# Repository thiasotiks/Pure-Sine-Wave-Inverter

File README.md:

# Pure-Sine-Wave-Inverter    
This repository includes codes for pure sine wave inverter @ 50 Hz, 220 V
It also contains the PCB design files in a seperate zip file

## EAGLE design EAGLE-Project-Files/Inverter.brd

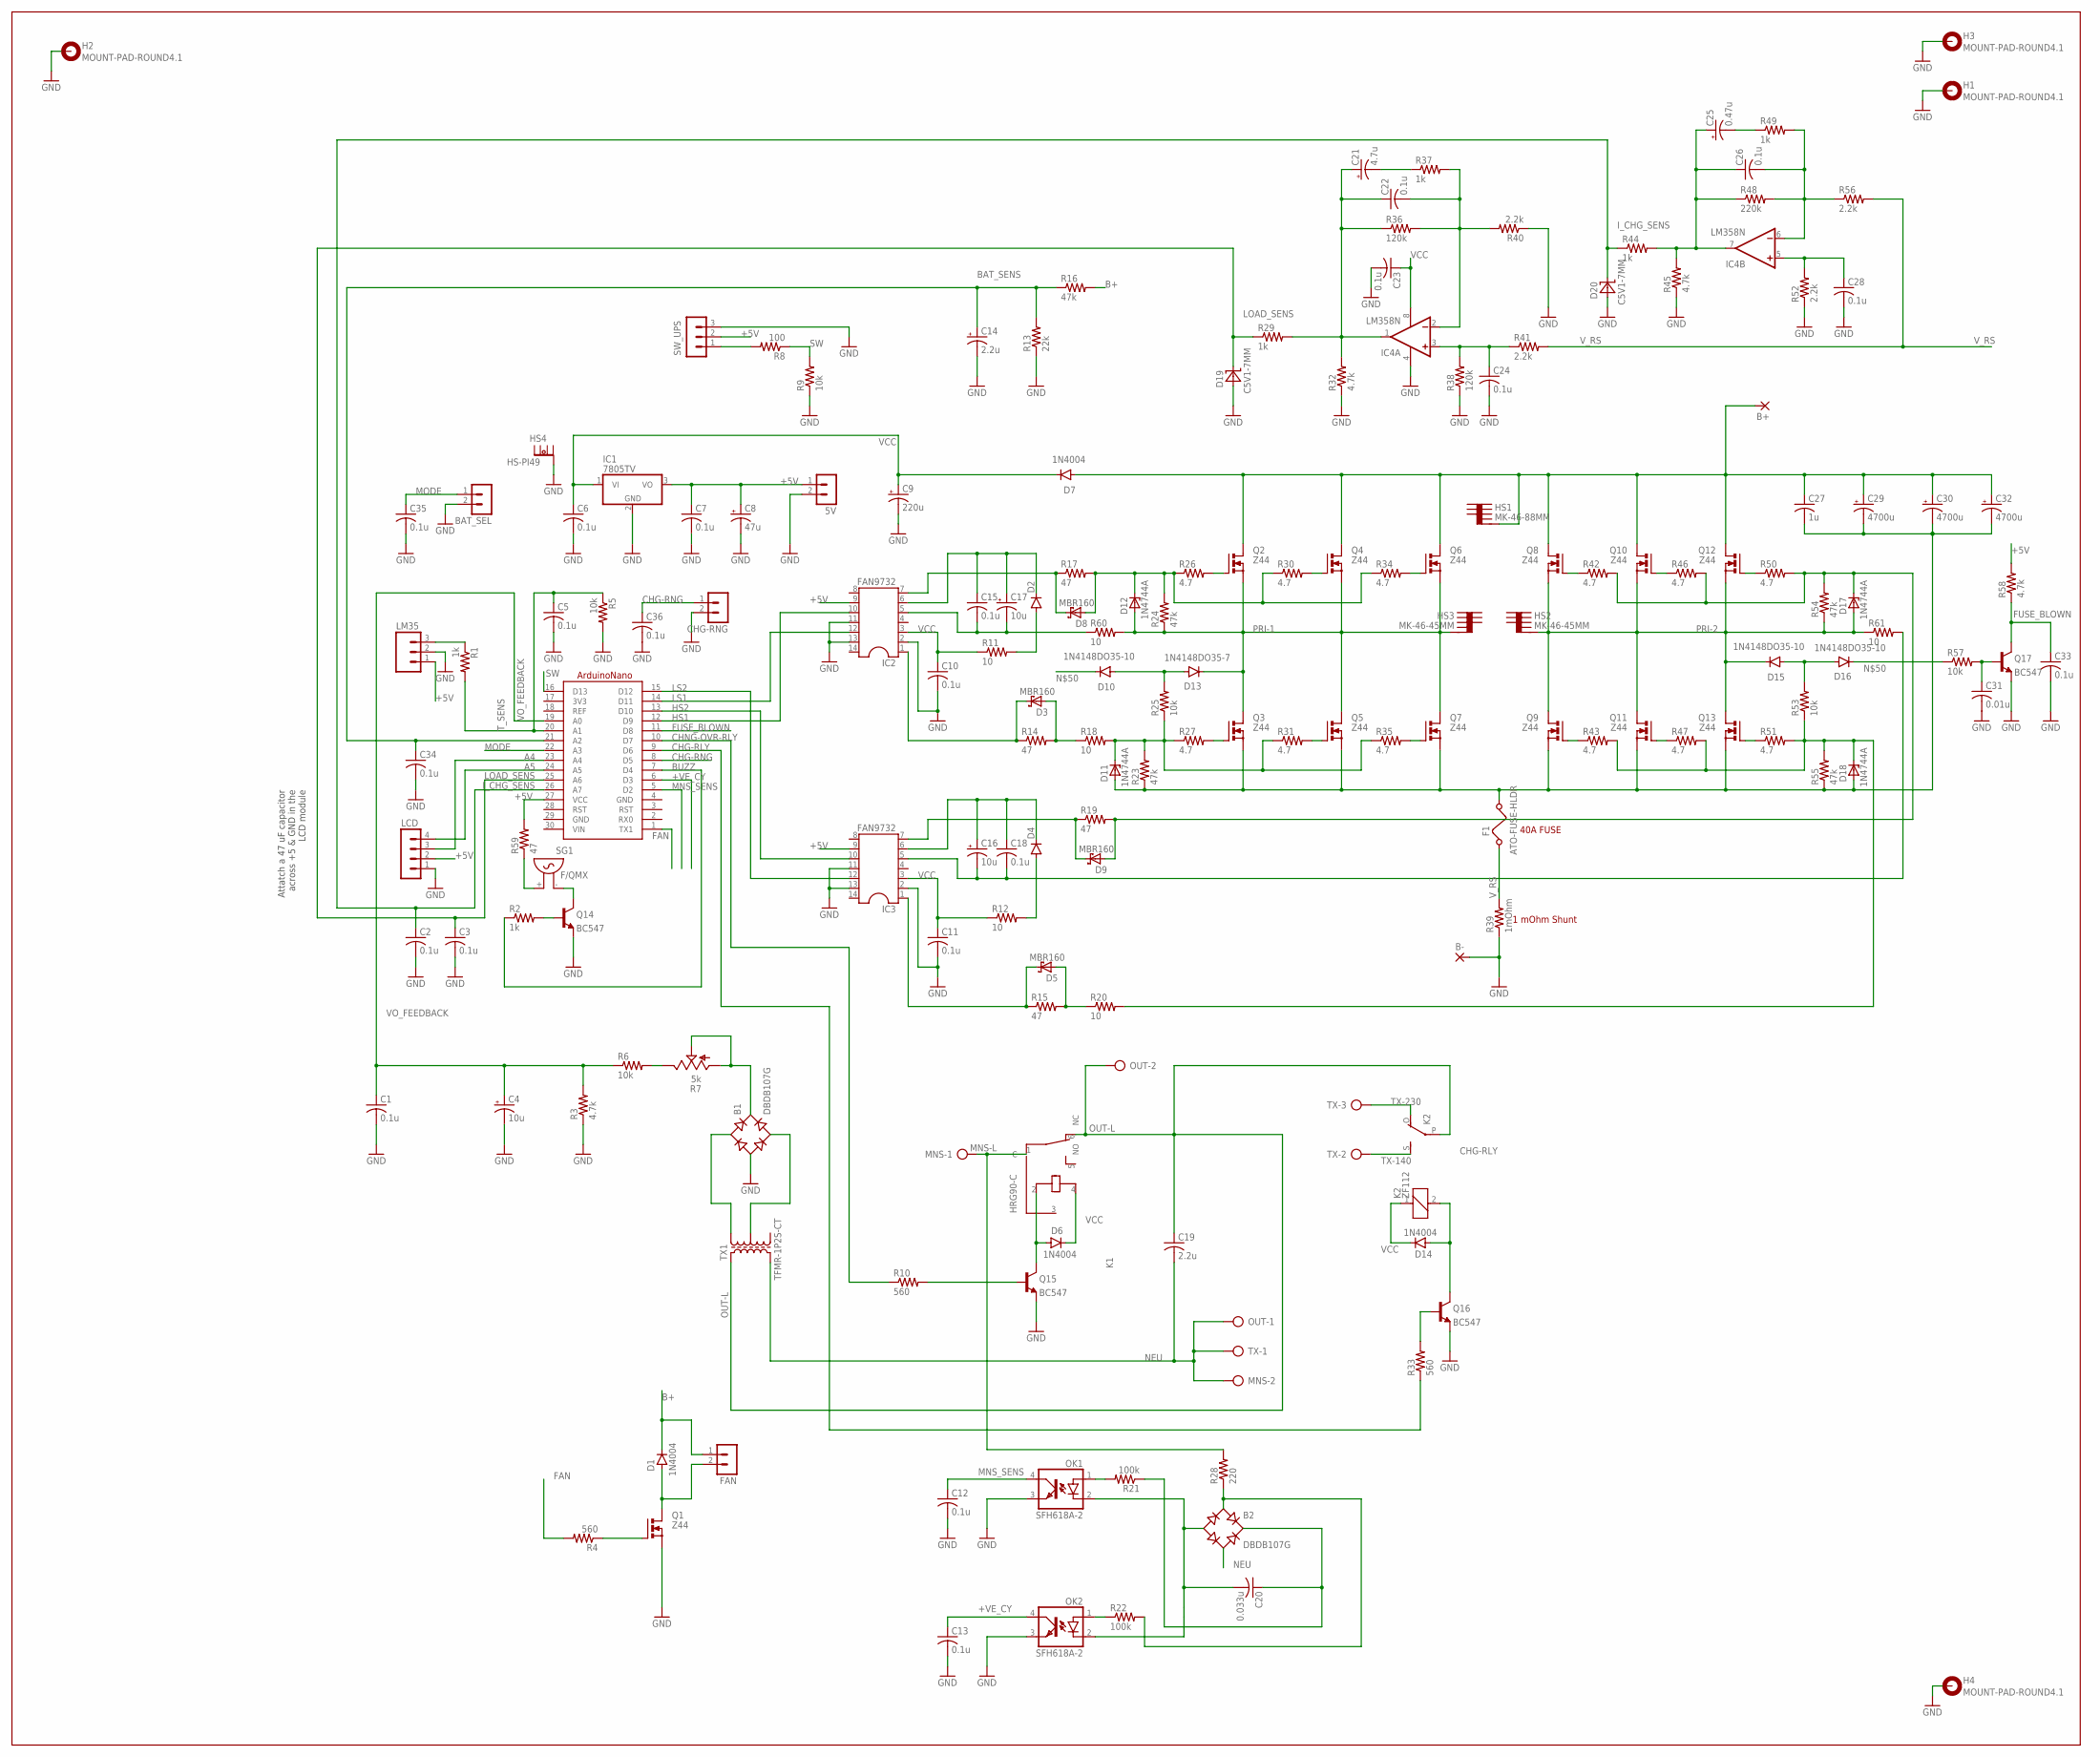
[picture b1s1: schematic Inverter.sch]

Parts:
5V: MA02-1
A1: ARDUINONANO-MIN-TXT; ARDUINONANO-MINIMUM-TXT
B1, B2: DBDB107G; DB
B+: 3,17/1,1
B-: 3,17/1,1
BAT_SEL: MA02-1
C1, C2, C3, C5, C6, C7, C10, C11, C12, C13, C15, C18, C22, C23, C24, C26, C28, C33, C34, C35, C36: 0.1u; C025-025X050
C4, C16, C17: 10u; E2,5-6E
C8: 47u; E2,5-6E
C9: 220u; E2,5-6E
C14: 2.2u; E2,5-6
C19: 2.2u; C230-85X245
C20: 0.033u; C050-025X075
C21: 4.7u; E2,5-6
C25: 0.47u; E2,5-6
C27: 1u; C225-113X268
C29, C30, C32: 4700u; EB20D
C31: 0.01u; C025-025X050
CHG-RNG: MA02-1
D1, D6, D7, D14: 1N4004; DO41-10
D2, D4, D10, D15, D16: 1N4148DO35-10; DO35-10
D3, D5, D8, D9: MBR160; DO41-10
D11, D12, D17, D18: 1N4744A; DO41Z10
D13: 1N4148DO35-7; DO35-7
D19, D20: C5V1-7MM; DO35-7
F1: ATO-FUSE-HLDR; ATO-FUSE-HOLDER
FAN: MA02-1
H1, H2, H3, H4: MOUNT-PAD-ROUND4.1; 4,1-PAD
HS1: MK-46-88MM
HS2, HS3: MK-46-45MM
HS4: HS-PI49; PI49-20MM
IC1: 7805TV; TO220V
IC2, IC3: FAN9732; SOCKET-14
IC4: LM358N; DIL08
K1: HRG90-C; T90-C
K2: ZF112
LCD: MA04-1
LM35: MA03; 03P
MNS: AK300/2
OK1, OK2: SFH618A-2; DIP4
OUT: AK300/2
Q1, Q2, Q3, Q4, Q5, Q6, Q7, Q8, Q9, Q10, Q11, Q12, Q13: Z44; TO220BV
Q14, Q15, Q16, Q17: BC547; TO92_LIN
R1, R2, R29, R37, R44, R49: 1k; 0207/10
R3, R32, R45, R58: 4.7k; 0207/10
R4, R10, R33: 560; 0207/10
R5, R6, R9, R25, R53, R57: 10k; 0207/10
R7: 5k; CA6V
R8: 100; 0207/10
R11, R12, R18, R20, R60, R61: 10; 0207/10
R13: 22k; 0207/10
R14, R15, R17, R19, R59: 47; 0207/10
R16, R23, R24, R54, R55: 47k; 0207/10
R21: 100k; 0411V
R22: 100k; 0411/15
R26, R27, R30, R31, R34, R35, R42, R43, R46, R47, R50, R51: 4.7; 0207/10
R28: 220; 0207/10
R36, R38: 120k; 0207/10
R39: 1mOhm; SHUNT-R
R40, R41, R52, R56: 2.2k; 0207/10
R48: 220k; 0207/10
SG1: F/QMX
SW_UPS: MA03-1
TX: AK300/3
TX1: TRANSFORMER-1P2S-CT; XFMR-1S2P-CT-41X34MM

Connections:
3V3: A1.17 (3V3)
+5V: 5V.1, A1.27 (VCC), C7.1, C8.+, IC1.3 (VO), IC2.9, IC3.9, LCD.2, LM35.1, R58.2, R59.2, SW_UPS.2
+VE_CY: A1.6 (D3), C13.1, OK2.4 (COL)
A4: A1.23 (A4), LCD.3
A5: A1.24 (A5), LCD.4
B+: B+.1, C27.1, C29.+, C30.+, C32.+, D1.C, D7.A, FAN.1, HS1.1, HS1.2, Q2.D, Q4.D, Q6.D, Q8.D, Q10.D, Q12.D, R16.2
BAT_SENS: A1.21 (A2), C14.+, C34.1, R13.2, R16.1
BUZZ: A1.7 (D4), R2.1
CHG-RLY: A1.9 (D6), R33.1
CHG-RNG: A1.8 (D5), C36.1, CHG-RNG.1
CHNG-OVR-RLY: A1.10 (D7), R10.1
FAN: A1.1 (TX1), R4.2
FUSE_BLOWN: A1.11 (D8), C33.1, Q17.3 (C), R58.1
GND: 5V.2, A1.4 (GND), A1.29 (GND), B1.-, B-.1, BAT_SEL.2, C1.2, C2.2, C3.2, C4.-, C5.2, C6.2, C7.2, C8.-, C9.-, C10.2, C11.2, C12.2, C13.2, C14.-, C23.2, C24.2, C28.2, C31.2, C33.2, C34.2, C35.2, C36.2, CHG-RNG.2, D19.A, D20.A, H1.B4,1, H2.B4,1, H3.B4,1, H4.B4,1, HS4.1, HS4.2, IC1.2 (GND), IC2.2, IC2.11, IC2.13, IC3.2, IC3.11, IC3.13, IC4.4 (V-), LCD.1, LM35.2, OK1.3 (EMIT), OK2.3 (EMIT), Q1.S, Q14.1 (E), Q15.1 (E), Q16.1 (E), Q17.1 (E), R3.1, R5.2, R9.1, R13.1, R32.1, R38.1, R39.P$1 (1), R40.1, R45.1, R52.1, SW_UPS.3
HS1: A1.12 (D9), IC2.10
HS2: A1.13 (D10), IC3.10
I_CHG_SENS: A1.26 (A7), C2.1, D20.C, R44.1
LOAD_SENS: A1.25 (A6), C3.1, D19.C, R29.1
LS1: A1.14 (D11), IC2.12
LS2: A1.15 (D12), IC3.12
MNS-L: K1.1 (C), MNS.1, R28.2
MNS_SENS: A1.5 (D2), C12.1, OK1.4 (COL)
MODE: A1.22 (A3), BAT_SEL.1, C35.1
unnamed: D4.A, R12.2
unnamed: Q15.2 (B), R10.2
unnamed: C15.1, C17.+, D2.C, IC2.6
unnamed: C16.+, C18.1, D4.C, IC3.6
unnamed: Q14.3 (C), SG1.- (1)
unnamed: D8.A, D12.C, R17.2, R24.2, R26.1, R30.1, R34.1
unnamed: D2.A, R11.2
unnamed: D8.C, IC2.7, R17.1
unnamed: D3.C, IC2.1, R14.1
unnamed: D9.C, IC3.7, R19.1
unnamed: D5.C, IC3.1, R15.1
unnamed: D11.C, R18.2, R23.2, R25.1, R27.1, R31.1, R35.1
unnamed: C27.2, C29.-, C30.-, C32.-, D11.A, D18.A, F1.P$2 (2), Q3.S, Q5.S, Q7.S, Q9.S, Q11.S, Q13.S, R23.1, R55.1
unnamed: D9.A, D17.C, R19.2, R42.2, R46.2, R50.2, R54.2
unnamed: D18.C, R20.2, R43.2, R47.2, R51.2, R53.1, R55.2
unnamed: Q2.G, R26.2
unnamed: C24.1, IC4.3 (+IN), R38.2, R41.1
unnamed: B1.AC1, TX1.10
unnamed: C16.-, C18.2, IC3.5, R61.2
unnamed: LM35.3, R1.1
unnamed: B1.AC2, TX1.8
unnamed: C22.2, IC4.2 (-IN), R36.2, R37.2, R40.2
unnamed: B1.+, R7.A, R7.S
unnamed: Q14.2 (B), R2.2
unnamed: R6.2, R7.E
unnamed: Q3.G, R27.2
unnamed: C15.2, C17.-, IC2.5, R60.1
unnamed: Q1.G, R4.1
unnamed: B2.AC1, R22.2, R28.1
unnamed: D1.A, FAN.2, Q1.D
unnamed: D6.A, K1.2 (COIL2), Q15.3 (C)
unnamed: Q13.G, R51.1
unnamed: D14.A, K2.2, Q16.3 (C)
unnamed: Q16.2 (B), R33.2
unnamed: Q12.G, R50.1
unnamed: OK1.1 (A), R21.2
unnamed: OK2.1 (A), R22.1
unnamed: B2.-, C20.2, OK1.2 (C), OK2.2 (C)
unnamed: B2.+, C20.1, R21.1
unnamed: C21.+, C22.1, IC4.1 (OUT), R29.2, R32.2, R36.1
unnamed: C21.-, R37.1
unnamed: Q9.G, R43.1
unnamed: D10.A, D13.A, R25.2
unnamed: Q4.G, R30.2
unnamed: Q6.G, R34.2
unnamed: Q8.G, R42.1
unnamed: Q10.G, R46.1
unnamed: Q11.G, R47.1
unnamed: Q5.G, R31.2
unnamed: D10.C, D16.C, R57.1
unnamed: Q7.G, R35.2
unnamed: D15.A, D16.A, R53.2
unnamed: D5.A, R15.2, R20.1
unnamed: D3.A, R14.2, R18.1
unnamed: C31.1, Q17.2 (B), R57.2
unnamed: R8.2, SW_UPS.1
unnamed: C26.2, IC4.6 (-IN), R48.2, R49.2, R56.1
unnamed: C25.+, C26.1, IC4.7 (OUT), R44.2, R45.2, R48.1
unnamed: C28.1, IC4.5 (+IN), R52.2
unnamed: C25.-, R49.1
unnamed: R59.1, SG1.+ (2)
NEU: B2.AC2, C19.2, MNS.2, OUT.1, TX.1, TX1.5
OUT-L: C19.1, K1.6 (NC), K2.P, OUT.2, TX1.1
PRI-1: D12.A, D13.C, HS3.1, HS3.2, Q2.S, Q3.D, Q4.S, Q5.D, Q6.S, Q7.D, R24.1, R60.2
PRI-2: D15.C, D17.A, HS2.1, HS2.2, Q8.S, Q9.D, Q10.S, Q11.D, Q12.S, Q13.D, R54.1, R61.1
REF: A1.18 (REF)
SW: A1.16 (D13), R8.1, R9.2
TX-140: K2.S, TX.2
TX-230: K2.O, TX.3
T_SENS: A1.20 (A1), C5.1, R1.2, R5.1
VCC: C6.1, C9.+, C10.1, C11.1, C23.1, D6.C, D7.C, D14.C, IC1.1 (VI), IC2.3, IC3.3, IC4.8 (V+), K1.4 (COIL1), K2.1, R11.1, R12.1
VIN: A1.30 (VIN)
VO_FEEDBACK: A1.19 (A0), C1.1, C4.+, R3.2, R6.1
V_RS: F1.P$1 (1), R39.P$2 (2), R41.2, R56.2

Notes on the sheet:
40A FUSE
1 mOhm Shunt
Attatch a 47 uF capacitor across +5 & GND in the LCD module

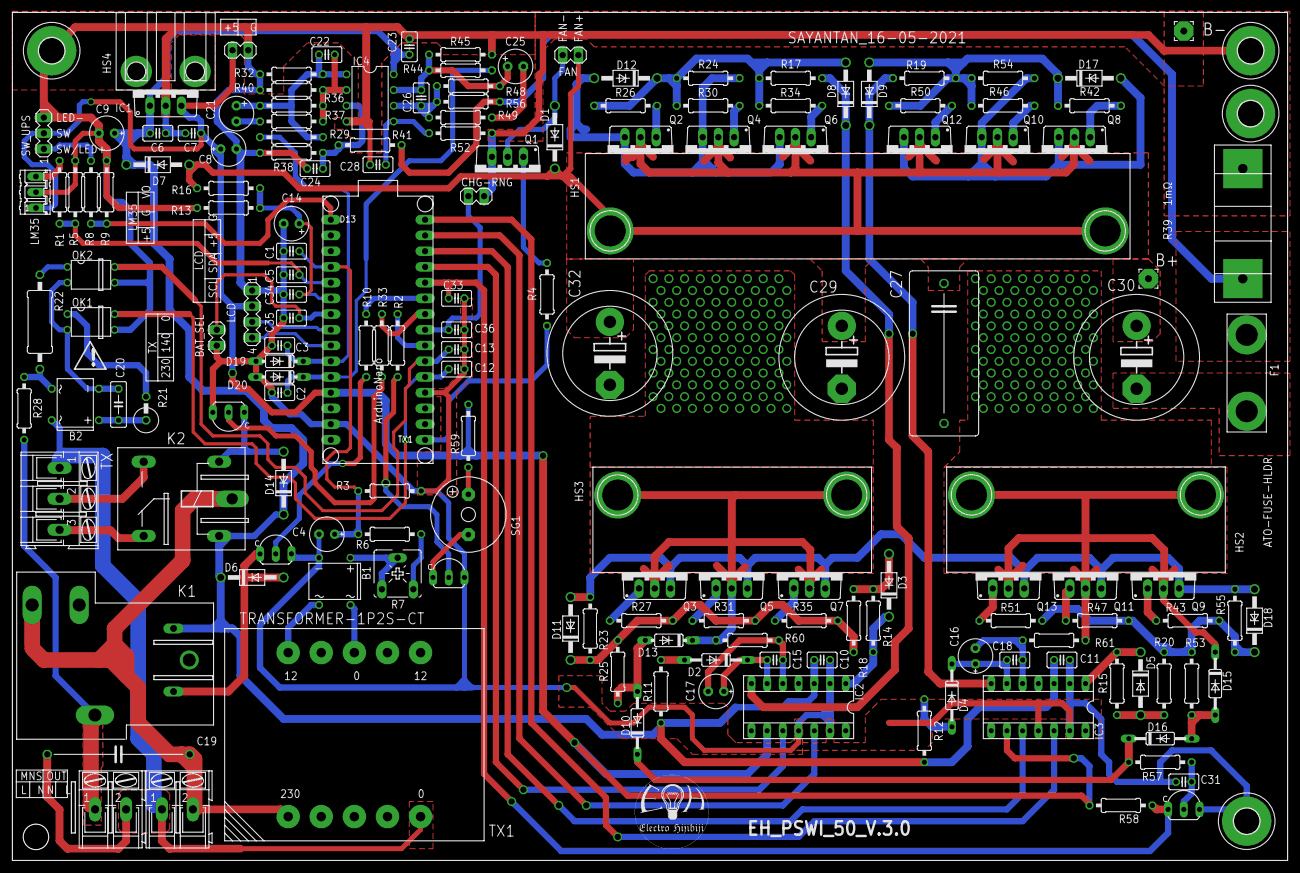
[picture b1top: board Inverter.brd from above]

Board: 2 copper layers, 205.8 x 136.8 mm, 168 parts (0 on the bottom side), 94 nets.
